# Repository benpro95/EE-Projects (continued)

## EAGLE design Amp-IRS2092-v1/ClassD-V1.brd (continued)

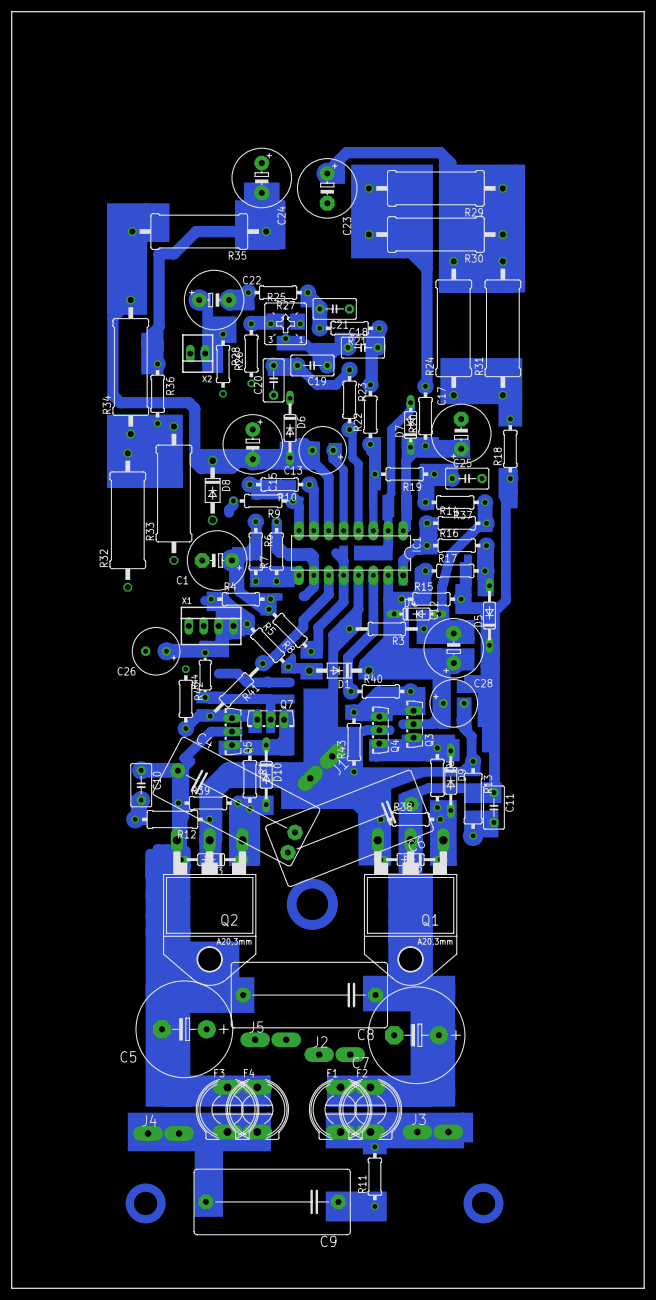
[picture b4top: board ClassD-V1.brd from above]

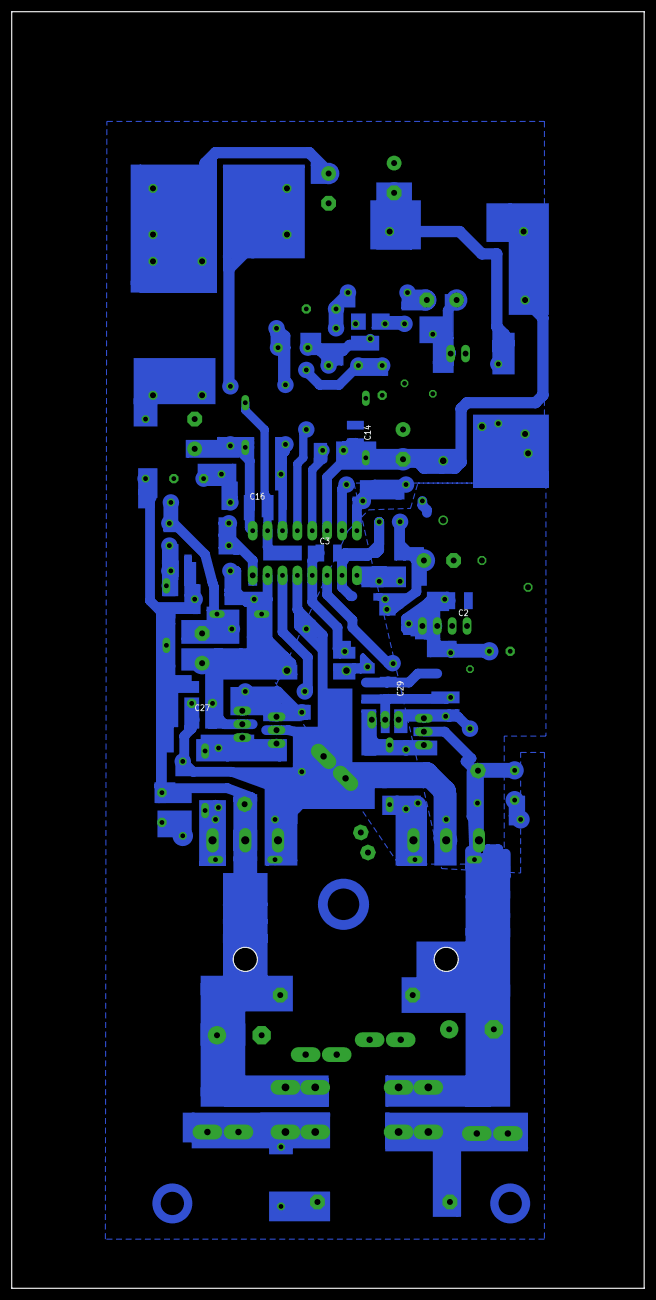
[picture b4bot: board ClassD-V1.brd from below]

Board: 2 copper layers, 107.9 x 217.9 mm, 101 parts (6 on the bottom side), 47 nets.

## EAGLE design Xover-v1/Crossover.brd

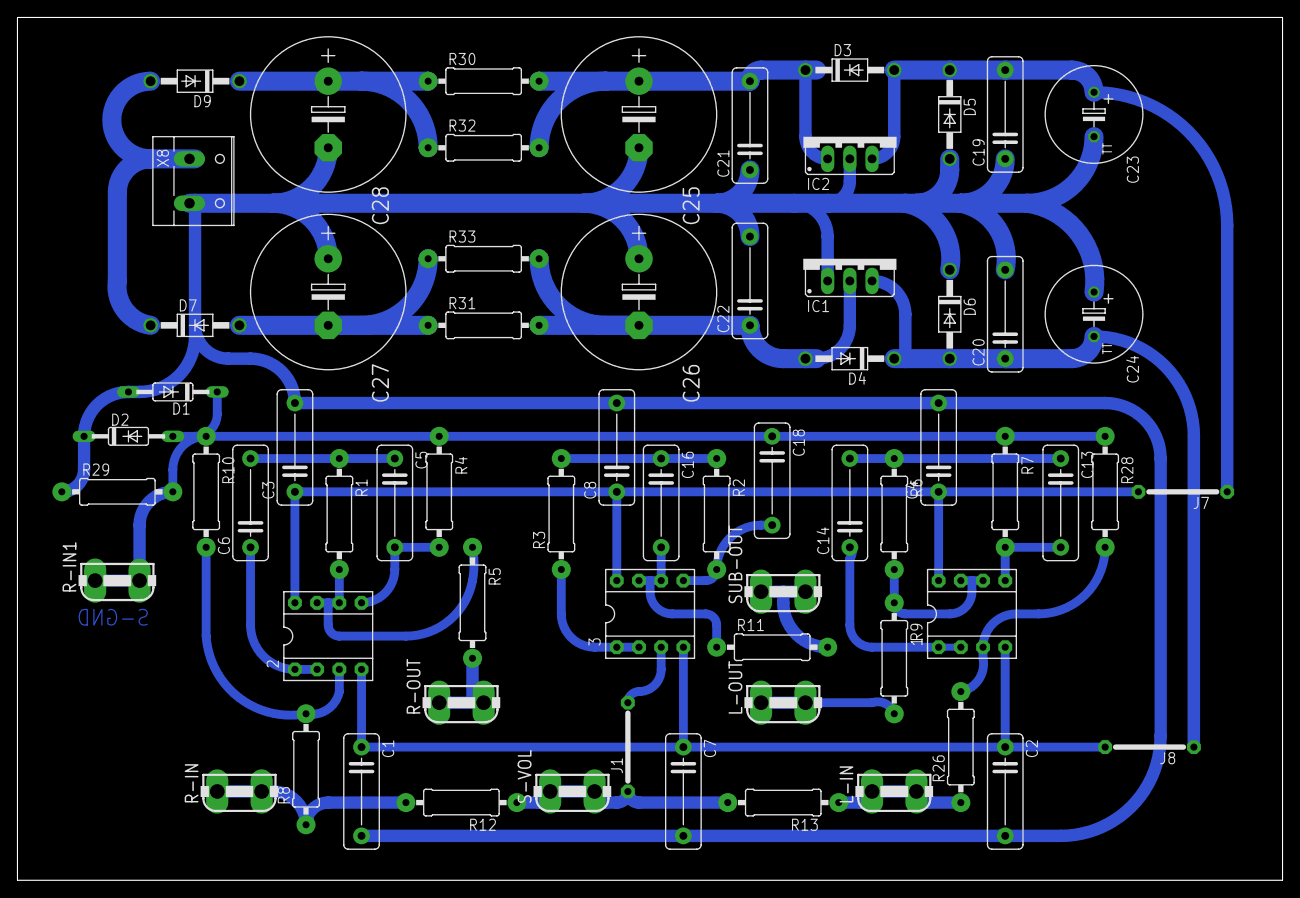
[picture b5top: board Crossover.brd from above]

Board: 2 copper layers, 144.8 x 98.7 mm, 66 parts (0 on the bottom side), 32 nets.

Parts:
1, 2, 3: OPA2132; DIP-8
C1, C2, C3, C4, C5, C6, C7, C8, C13, C14, C16, C18, C19, C20, C21, C22: .1; C102-043X133
C23, C24: 470uF; TT5D11
C25, C26, C27, C28: 4700uF; E7,5-18
D1, D2: 1N4148; DO35-10
D3, D4, D5, D6, D7, D9: 1N4004; DO41-10
IC1: 7915; 79XXS
IC2: 7815; 78XXS
J1, J7, J8: J10MM; 10
L-IN: QFIT; FASTON
L-OUT: QFIT; FASTON
R1, R2, R3, R4, R6, R7: 8.2k; 0309/12
R5, R9, R11: 100R; 0309/12
R8, R26: 2.2K; 0309/12
R10, R28: 100K; 0309/12
R12, R13: 10K; 0309/12
R29: 10R; 0309/12
R30, R31, R32, R33: 22R; 0309/12
R-IN, R-IN1: QFIT; FASTON
R-OUT: QFIT; FASTON
S-VOL: QFIT; FASTON
SUB-OUT: QFIT; FASTON
X8: 16VAC; W237-132

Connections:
+15V: 1.8, 2.8, 3.8, C3.1, C4.1, C8.1, J7.2
-15V: 1.4, 2.4, 3.4, C1.1, C2.1, C7.1, J8.2
AGND: C18.1, D1.C, D2.A, R4.1, R7.1, R10.1, R28.1, R29.2, R-IN1.1, R-IN1.2
GND: C1.2, C2.2, C3.2, C4.2, C7.2, C8.2, C19.1, C20.2, C21.1, C22.2, C23.-, C24.+, C25.-, C26.+, C27.+, C28.-, D1.A, D2.C, D5.A, D6.C, IC1.GND, IC2.GND, R29.1, X8.2
unnamed: 1.1, 1.2, C14.1
unnamed: 3.6, 3.7, C16.2, R11.1
unnamed: 1.6, 1.7, R6.2, R9.1
unnamed: 2.1, 2.2, C6.1
unnamed: 2.6, 2.7, R1.2, R5.1
unnamed: 2.5, C5.2, R4.2
unnamed: 3.5, C18.2, R2.2
unnamed: C5.1, C6.2, R1.1
unnamed: R5.2, R-OUT.1, R-OUT.2
unnamed: 2.3, R8.2, R10.2
unnamed: R8.1, R12.2, R-IN.1, R-IN.2
unnamed: 1.5, C13.2, R7.2
unnamed: 3.1, 3.2, R3.1
unnamed: C13.1, C14.2, R6.1
unnamed: C16.1, R2.1, R3.2
unnamed: R11.2, SUB-OUT.1, SUB-OUT.2
unnamed: L-OUT.1, L-OUT.2, R9.2
unnamed: 3.3, J1.2
unnamed: J1.1, R12.1, R13.2, S-VOL.1, S-VOL.2
unnamed: 1.3, R26.2, R28.2
unnamed: L-IN.1, L-IN.2, R13.1, R26.1
unnamed: C27.-, D7.A, R31.1, R33.1
unnamed: C21.2, C25.+, D3.C, IC2.IN, R30.2, R32.2
unnamed: C19.2, C23.+, D3.A, D5.C, IC2.OUT, J7.1
unnamed: C22.1, C26.-, D4.A, IC1.IN, R31.2, R33.2
unnamed: D7.C, D9.A, X8.1
unnamed: C28.+, D9.C, R30.1, R32.1
unnamed: C20.1, C24.-, D4.C, D6.A, IC1.OUT, J8.1

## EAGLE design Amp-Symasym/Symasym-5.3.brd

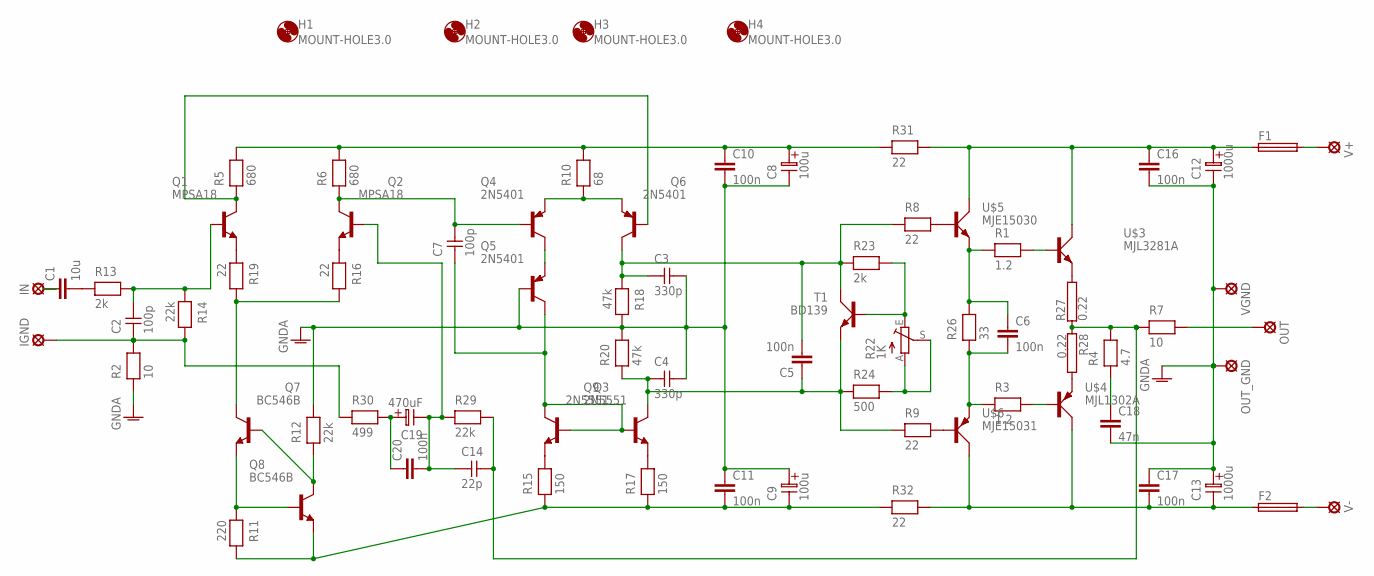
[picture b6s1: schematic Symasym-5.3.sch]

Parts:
C1: 10u; C5B7.2
C2, C7: 100p; C-3,75
C3, C4: 330p; C-3,75
C5: 100n; C5B2.5
C6, C16, C17, C20: 100n; C5B3
C8, C9: 100u; ES-5
C10, C11: 100n; C5B3.5
C12, C13: 1000u; ES-7,5
C14: 22p; C-3,75
C18: 47n; C5B3
C19: 470uF; ES-5
F1, F2: SHK20L
H1, H2, H3, H4: MOUNT-HOLE3.0; 3,0
IGND: SE11
IN: SE11
OUT: SE11
OUT_GND: SE11
Q1, Q2: MPSA18; TO92-EBC@1
Q3, Q9: 2N5551; TO92-EBC@1
Q4, Q5, Q6: 2N5401; TO92-EBC
Q7, Q8: BC546B; TO92-EBC
R1, R3: 1.2; R-18
R2: 10; R-10
R4: 4.7; R-18
R5, R6: 680; R-10
R7: 10; R-18
R8, R9, R31, R32: 22; R-10
R10: 68; R-10
R11: 220; RS-2,5
R12, R29: 22k; R-10
R13: 2k; RS-2,5
R14: 22k; RS-2,5
R15, R17: 150; R-10
R16, R19: 22; RS-2,5
R18, R20: 47k; RS-2,5
R22: 1K; LI10
R23: 2k; R-10
R24: 500; R-10
R26: 33; R-10
R27, R28: 0.22; KH208R-8
R30: 499; R-10
T1: BD139; TO126AV
U$3: MJL3281A; TO247BV
U$4: MJL1302A; TO247BV
U$5: MJE15030; TO220AV
U$6: MJE15031; TO220AV
V+: SE11
V-: SE11
VGND: SE11

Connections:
+24V: C8.1, C10.1, R5.2, R6.2, R10.2, R31.1
-24V: C9.2, C11.2, Q8.E, R11.2, R15.1, R17.1, R32.1
unnamed: Q3.E, R15.2
unnamed: R1.2, U$3.G (B)
unnamed: Q7.C, R16.2, R19.2
unnamed: Q4.C, Q5.E
unnamed: R3.2, U$4.G (B)
unnamed: Q9.E, R17.2
unnamed: C12.1, C16.1, F1.1A, R31.2, U$3.D (C), U$5.C
unnamed: C7.P$2 (2), Q2.C, Q4.B, R6.1
unnamed: C3.P$1 (1), C5.2, Q6.C, R8.1, R18.1, R23.1, T1.C
unnamed: C7.P$1 (1), Q3.B, Q3.C, Q5.C, Q9.B
unnamed: R8.2, U$5.B
unnamed: R9.2, U$6.B
unnamed: C1.2, R13.1
unnamed: C18.1, R4.1
unnamed: C2.P$1 (1), IGND.MP, R2.2, R14.2, R30.1
unnamed: Q7.E, Q8.B, R11.1
unnamed: Q4.E, Q6.E, R10.1
unnamed: Q7.B, Q8.C, R12.1
unnamed: C1.1, IN.MP
unnamed: C2.P$2 (2), Q1.B, R13.2, R14.1
unnamed: Q1.C, Q6.B, R5.1
unnamed: C19.1, C20.1, R30.2
unnamed: R22.E, R23.2, T1.B
unnamed: R22.A, R22.S, R24.2
unnamed: C13.2, C17.2, F2.1A, R32.2, U$4.D (C), U$6.C
unnamed: C14.P$1 (1), C19.2, C20.2, Q2.B, R29.1
unnamed: OUT.MP, R7.2
unnamed: R27.2, U$3.S (E)
unnamed: R28.2, U$4.S (E)
unnamed: C14.P$2 (2), R4.2, R7.1, R27.1, R28.1, R29.2
unnamed: F2.2A, V-.MP
unnamed: C4.P$1 (1), C5.1, Q9.C, R9.1, R20.1, R24.1, T1.E
unnamed: F1.2A, V+.MP
unnamed: C6.1, R1.1, R26.2, U$5.E
unnamed: C6.2, R3.1, R26.1, U$6.E
unnamed: C3.P$2 (2), C4.P$2 (2), C8.2, C9.1, C10.2, C11.1, C12.2, C13.1, C16.2, C17.1, C18.2, OUT_GND.MP, Q5.B, R2.1, R12.2, R18.2, R20.2, VGND.MP
unnamed: Q2.E, R16.1
unnamed: Q1.E, R19.1

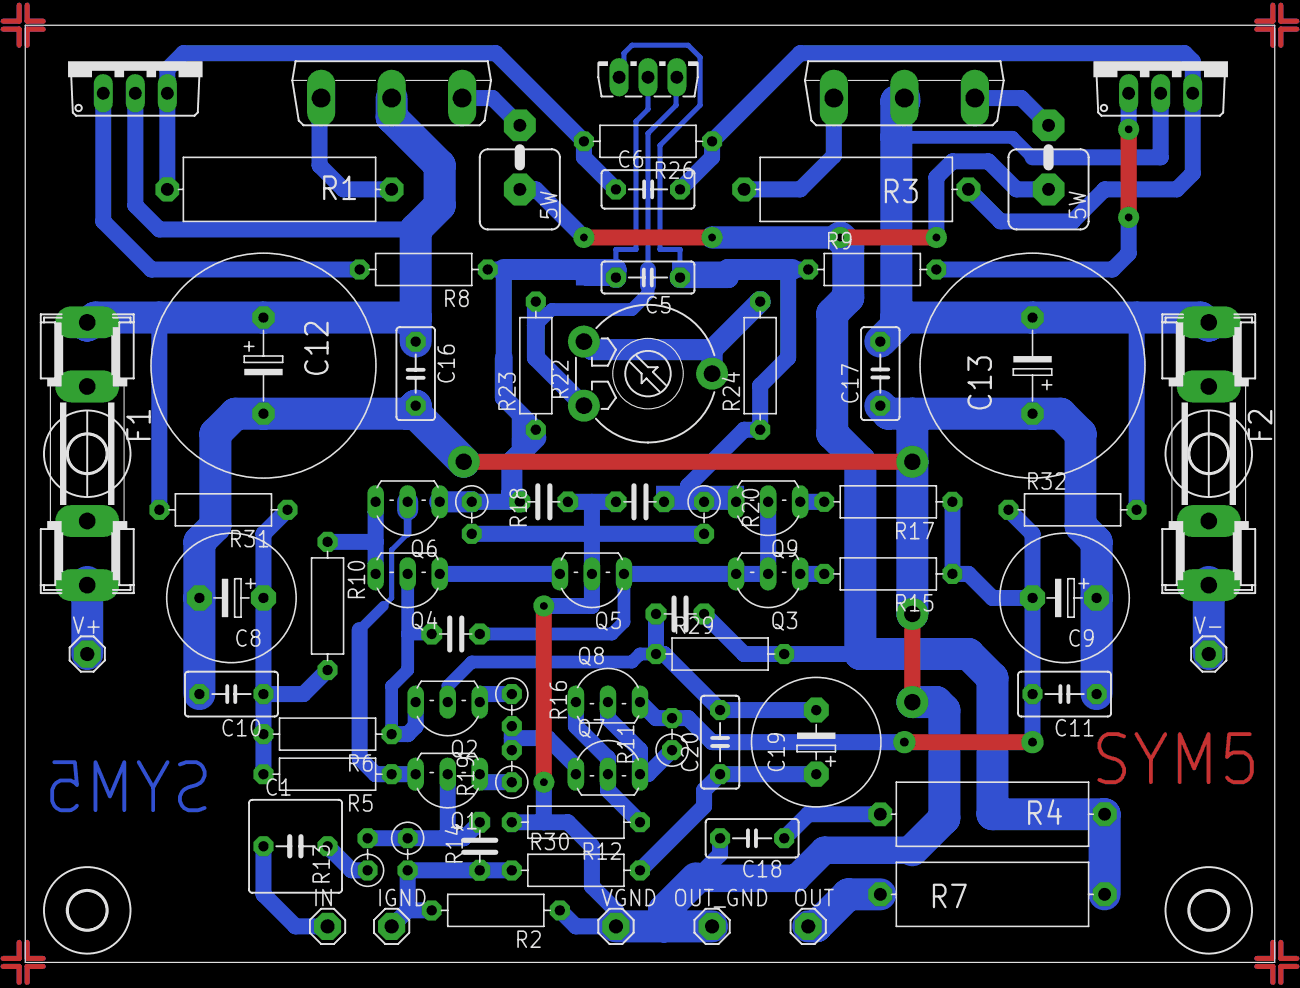
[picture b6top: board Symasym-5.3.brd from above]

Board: 2 copper layers, 99.0 x 74.3 mm, 76 parts (0 on the bottom side), 40 nets.

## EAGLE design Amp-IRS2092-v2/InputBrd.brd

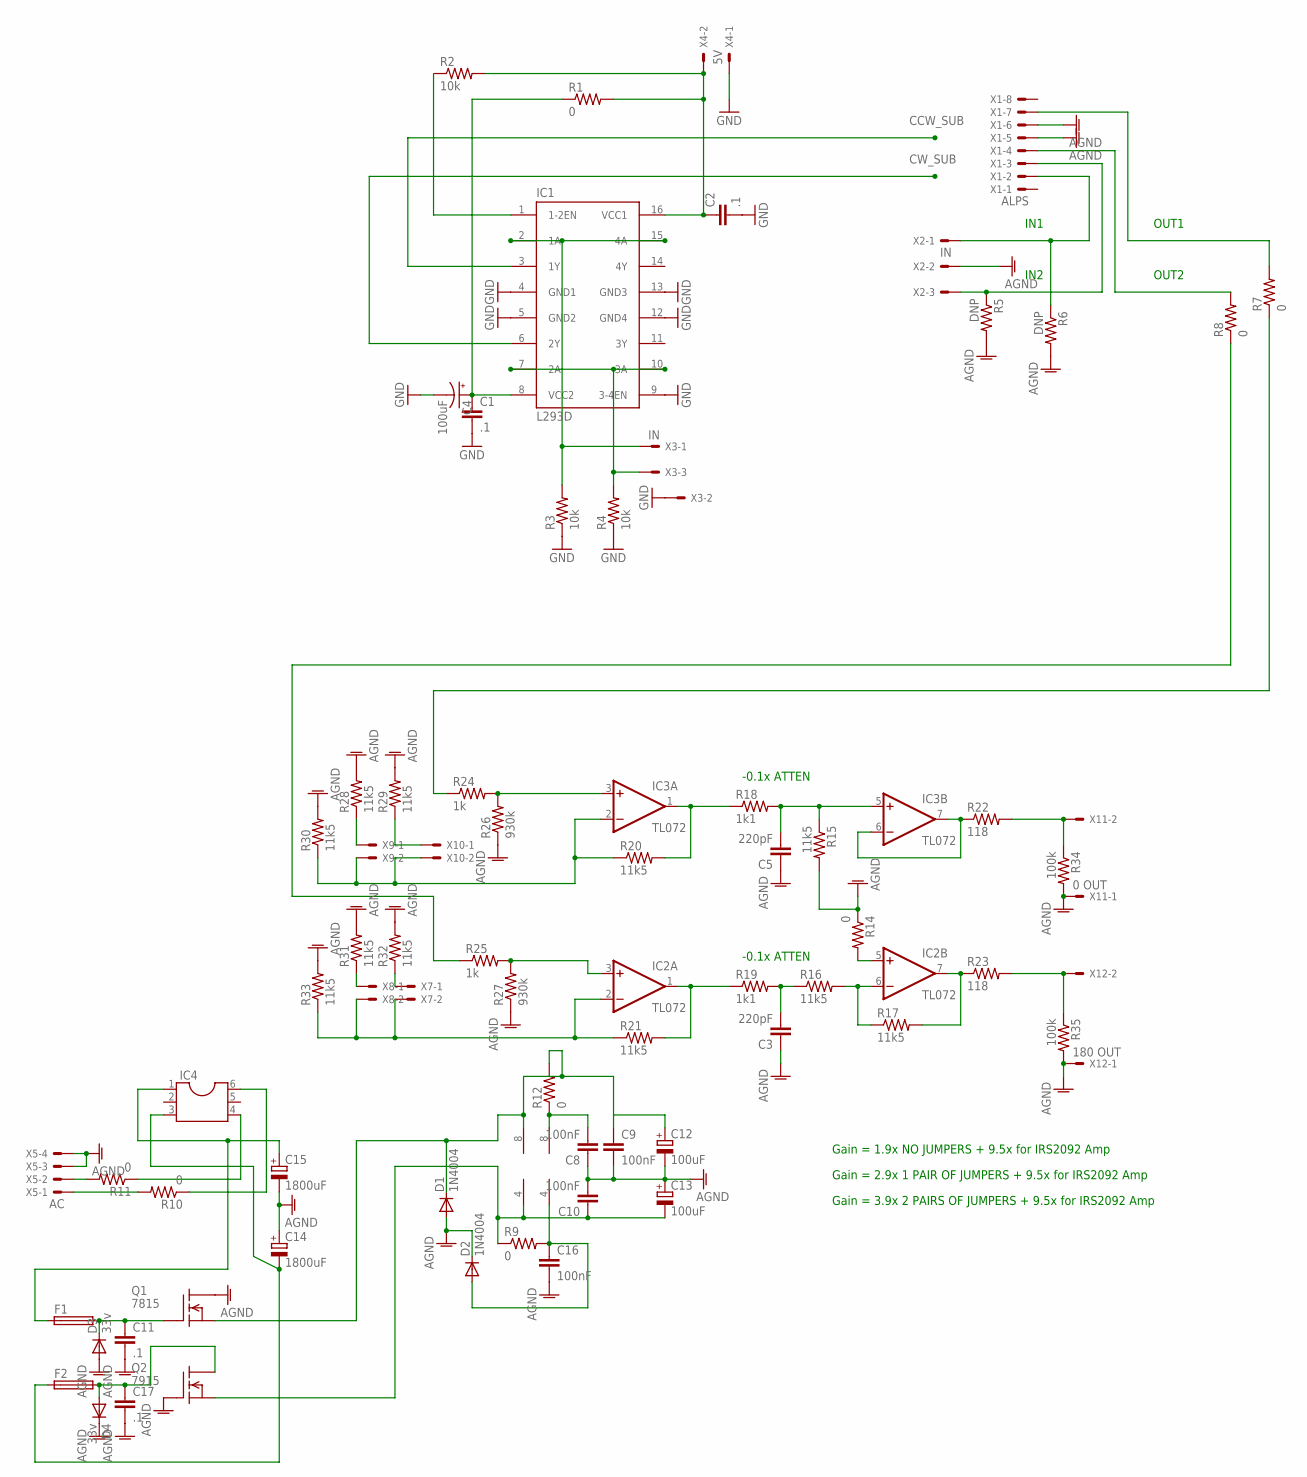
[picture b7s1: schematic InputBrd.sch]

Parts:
C1, C2, C11, C17: .1; C1210
C3, C5: 220pF; C050-035X075
C4: 100uF; E2,5-6E
C8, C9, C10, C16: 100nF; C1210
C12, C13: 100uF; E3,5-10
C14, C15: 1800uF; E7,5-16
D1, D2: 1N4004; DO41-10
D3, D4: 33v; TO220ACS
F1, F2: 19560
IC1: L293D; DIL16
IC2, IC3: TL072; DIL08
IC4: DIL6; DIL06
Q1: 7815; TO220
Q2: 7915; TO220
R1: 0; 0207/15
R2, R3, R4: 10k; R1210
R5, R6: DNP; 0309/10
R7, R8, R14: 0; 0309/12
R9, R12: 0; 0309/10
R10, R11: 0; 0309V
R15: 11k5; 0309/12
R16, R17, R20, R21, R28, R29, R30, R31, R32, R33: 11k5; 0309/10
R18, R19: 1k1; 0309/12
R22: 118; 0309/12
R23: 118; 0309/10
R24: 1k; 0411/15
R25: 1k; 0309/12
R26, R27: 930k; 0309/10
R34: 100k; 0309/12
R35: 100k; 0309/10
X1: ALPS; 22-23-2081
X2, X3: IN; 22-23-2031
X4: 5V; 22-23-2021
X5: AC; 5566-4
X7, X8, X9, X10: 22-23-2021
X11: 0 OUT; 22-23-2021
X12: 180 OUT; 22-23-2021

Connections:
AGND: C3.1, C5.1, C8.1, C9.2, C10.2, C11.2, C12.-, C13.+, C14.+, C15.-, C16.2, C17.2, D1.A, D2.C, D3.A, D4.C, Q1.2 (D), Q2.1 (G), R5.2, R6.2, R14.1, R15.2, R26.1, R27.1, R28.2, R29.2, R30.2, R31.2, R32.2, R33.2, R34.2, R35.2, X1.5, X1.6, X2.2, X5.3, X5.4, X11.1, X12.1
CCW_SUB: IC1.3 (1Y)
CW_SUB: IC1.6 (2Y)
GND: C1.2, C2.2, C4.-, IC1.4 (GND1), IC1.5 (GND2), IC1.9 (3-4EN), IC1.12 (GND4), IC1.13 (GND3), R3.1, R4.1, X3.2, X4.1
unnamed: IC1.7 (2A), IC1.10 (3A), R4.2, X3.3
unnamed: IC1.2 (1A), IC1.15 (4A), R3.2, X3.1
unnamed: R6.1, X1.2, X2.1
unnamed: R7.2, X1.7
unnamed: R5.1, X1.3, X2.3
unnamed: R7.1, R24.1
unnamed: IC1.1 (1-2EN), R2.1
unnamed: C1.1, C4.+, IC1.8 (VCC2), R1.1
unnamed: R8.2, X1.4
unnamed: C11.1, D3.C, F1.2, Q1.1 (G)
unnamed: C2.1, IC1.16 (VCC1), R1.2, R2.2, X4.2
unnamed: C17.1, D4.A, F2.2, Q2.2 (D)
unnamed: C16.1, D2.A, IC3.4 (V-), R9.2
unnamed: C8.2, IC3.8 (V+), R12.1
unnamed: R11.2, X5.2
unnamed: R10.2, X5.1
unnamed: IC4.6, R10.1
unnamed: IC4.4, R11.1
unnamed: C15.+, F1.1, IC4.1
unnamed: C14.-, F2.1, IC4.3
unnamed: C9.1, C12.+, D1.C, IC2.8 (V+), Q1.3 (S), R12.2
unnamed: C10.1, C13.-, IC2.4 (V-), Q2.3 (S), R9.1
unnamed: IC3.6 (-IN), IC3.7 (OUT), R22.1
unnamed: IC2.5 (+IN), R14.2
unnamed: C5.2, IC3.5 (+IN), R15.1, R18.2
unnamed: IC2.6 (-IN), R16.2, R17.1
unnamed: IC2.7 (OUT), R17.2, R23.1
unnamed: C3.2, R16.1, R19.2
unnamed: IC3.1 (OUT), R18.1, R20.2
unnamed: IC2.1 (OUT), R19.1, R21.2
unnamed: IC3.3 (+IN), R24.2, R26.2
unnamed: IC3.2 (-IN), R20.1, R30.1, X9.2, X10.2
unnamed: IC2.2 (-IN), R21.1, R33.1, X7.2, X8.2
unnamed: IC2.3 (+IN), R25.2, R27.2
unnamed: R31.1, X8.1
unnamed: R32.1, X7.1
unnamed: R29.1, X10.1
unnamed: R28.1, X9.1
unnamed: R22.2, R34.1, X11.2
unnamed: R23.2, R35.1, X12.2
unnamed: R8.1, R25.1

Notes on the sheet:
IN1
IN2
OUT2
OUT1
Gain = 1.9x NO JUMPERS + 9.5x for IRS2092 Amp
Gain = 2.9x 1 PAIR OF JUMPERS + 9.5x for IRS2092 Amp
Gain = 3.9x 2 PAIRS OF JUMPERS + 9.5x for IRS2092 Amp
-0.1x ATTEN

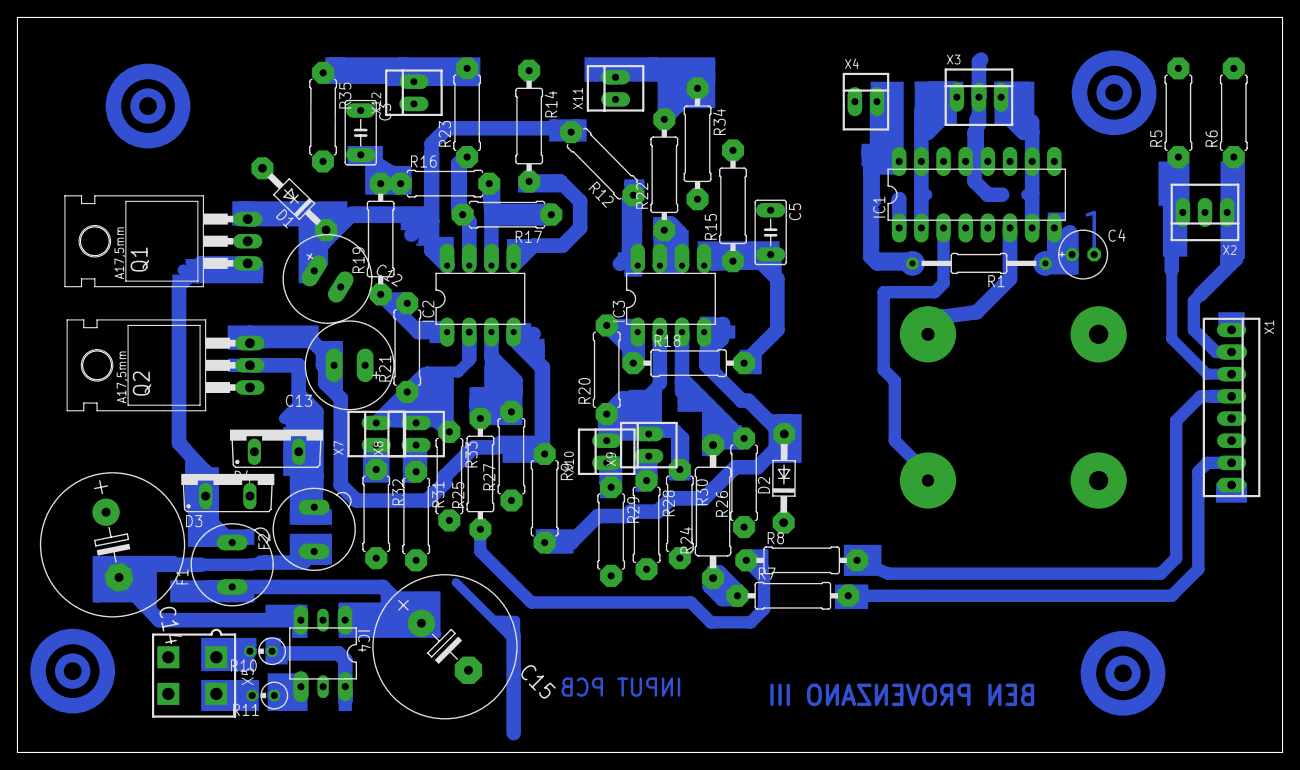
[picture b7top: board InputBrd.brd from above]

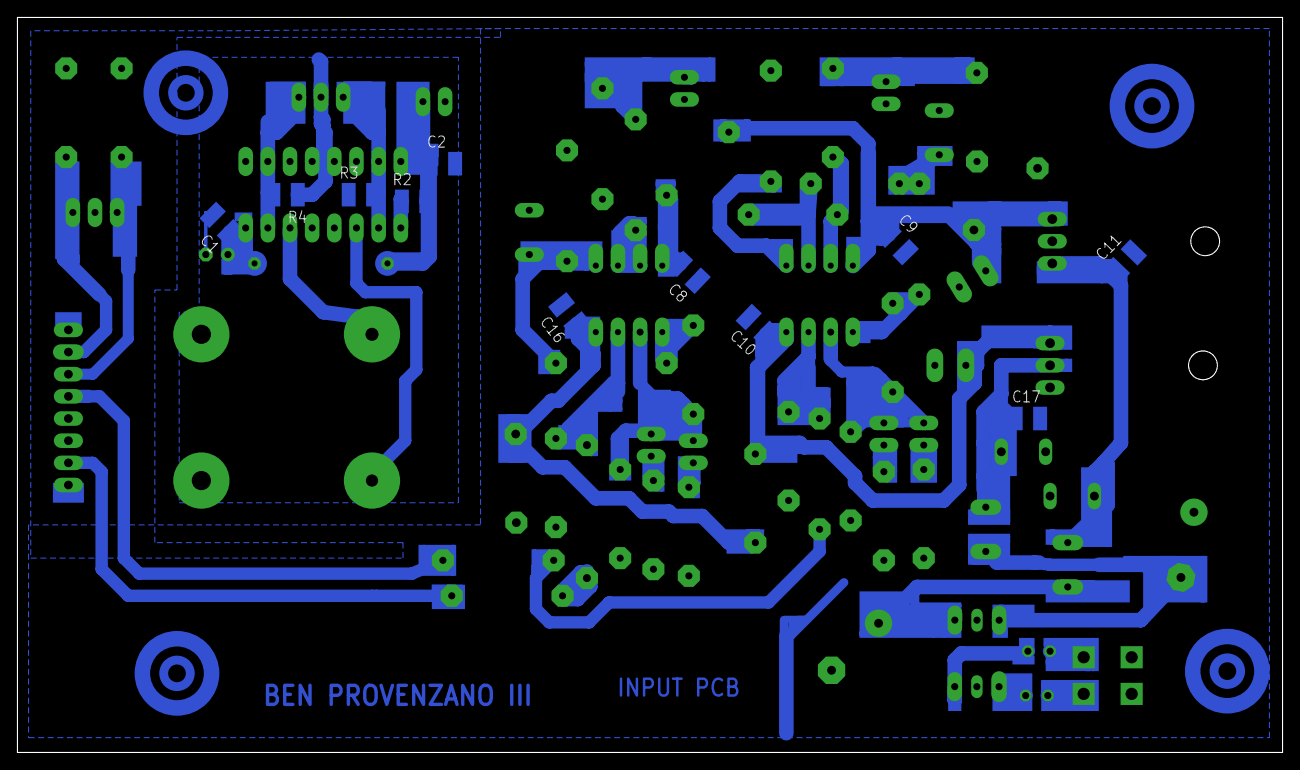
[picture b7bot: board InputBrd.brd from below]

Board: 2 copper layers, 145.0 x 84.3 mm, 72 parts (11 on the bottom side), 43 nets.

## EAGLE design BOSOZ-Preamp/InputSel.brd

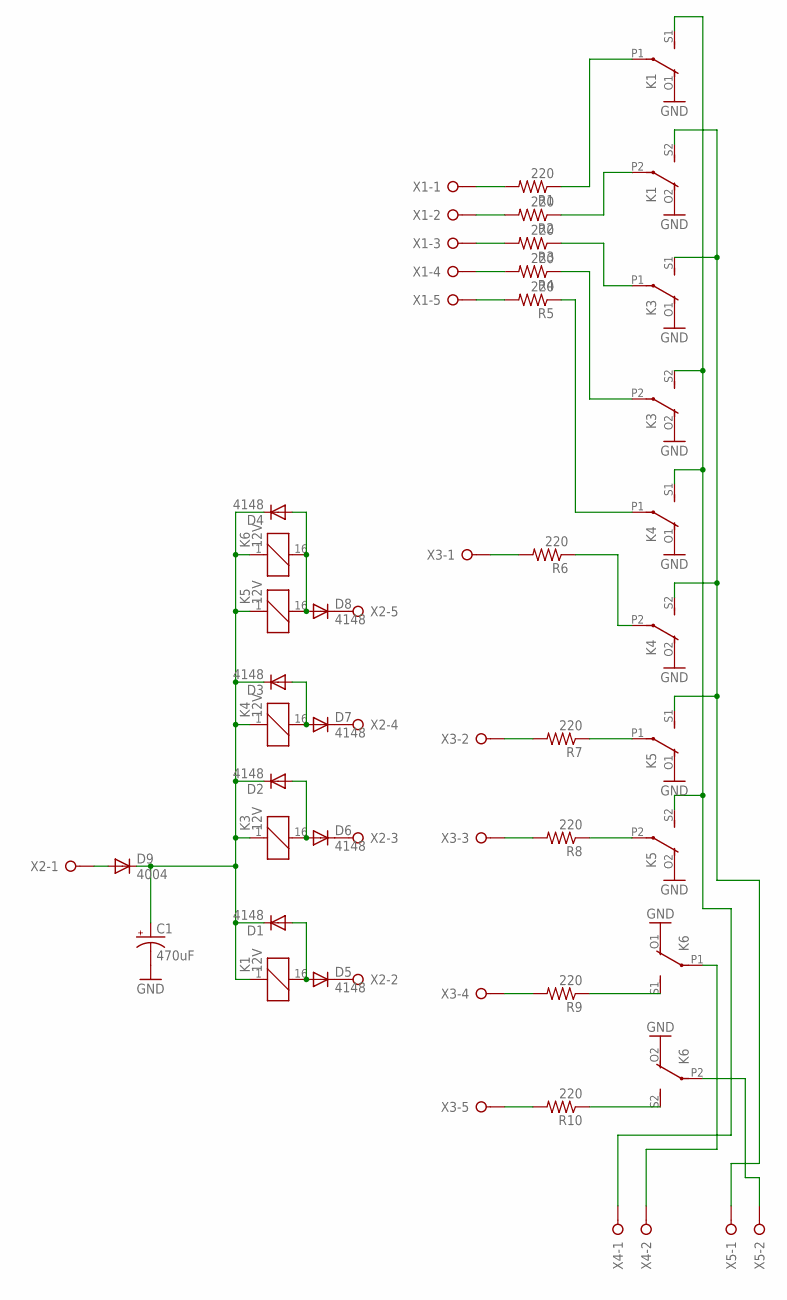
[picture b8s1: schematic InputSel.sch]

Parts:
C1: 470uF; E5-10,5
D1, D2, D3, D4, D5, D6, D7, D8: 4148; DO35-7
D9: 4004; DO35-10
K1, K3, K4, K5, K6: 12V; G6A-234P
R1, R2, R3, R4, R5, R6, R7, R8, R9, R10: 220; 0207/10
X1, X2, X3: W237-05P; W237-5P
X4, X5: W237-02P; W237-132

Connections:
GND: C1.-, K1.O1 (O), K1.O2 (O), K3.O1 (O), K3.O2 (O), K4.O1 (O), K4.O2 (O), K5.O1 (O), K5.O2 (O), K6.O1 (O), K6.O2 (O)
unnamed: K3.P1, R3.1
unnamed: R1.2, X1.1
unnamed: K3.P2, R4.1
unnamed: R2.2, X1.2
unnamed: K1.S1 (S), K3.S2 (S), K4.S1 (S), K5.S2 (S), X4.1
unnamed: R3.2, X1.3
unnamed: R4.2, X1.4
unnamed: K1.S2 (S), K3.S1 (S), K4.S2 (S), K5.S1 (S), X5.1
unnamed: K1.P2, R2.1
unnamed: K1.P1, R1.1
unnamed: R5.2, X1.5
unnamed: K4.P1, R5.1
unnamed: K5.P2, R8.1
unnamed: K5.P1, R7.1
unnamed: K4.P2, R6.1
unnamed: R6.2, X3.1
unnamed: R7.2, X3.2
unnamed: R8.2, X3.3
unnamed: R9.2, X3.4
unnamed: K6.S1 (S), R9.1
unnamed: R10.2, X3.5
unnamed: K6.S2 (S), R10.1
unnamed: C1.+, D1.C, D2.C, D3.C, D4.C, D9.C, K1.1, K3.1, K4.1, K5.1, K6.1
unnamed: K6.P1, X4.2
unnamed: K6.P2, X5.2
unnamed: D4.A, D8.A, K5.16 (2), K6.16 (2)
unnamed: D1.A, D5.A, K1.16 (2)
unnamed: D2.A, D6.A, K3.16 (2)
unnamed: D3.A, D7.A, K4.16 (2)
unnamed: D5.C, X2.2
unnamed: D6.C, X2.3
unnamed: D8.C, X2.5
unnamed: D7.C, X2.4
unnamed: D9.A, X2.1

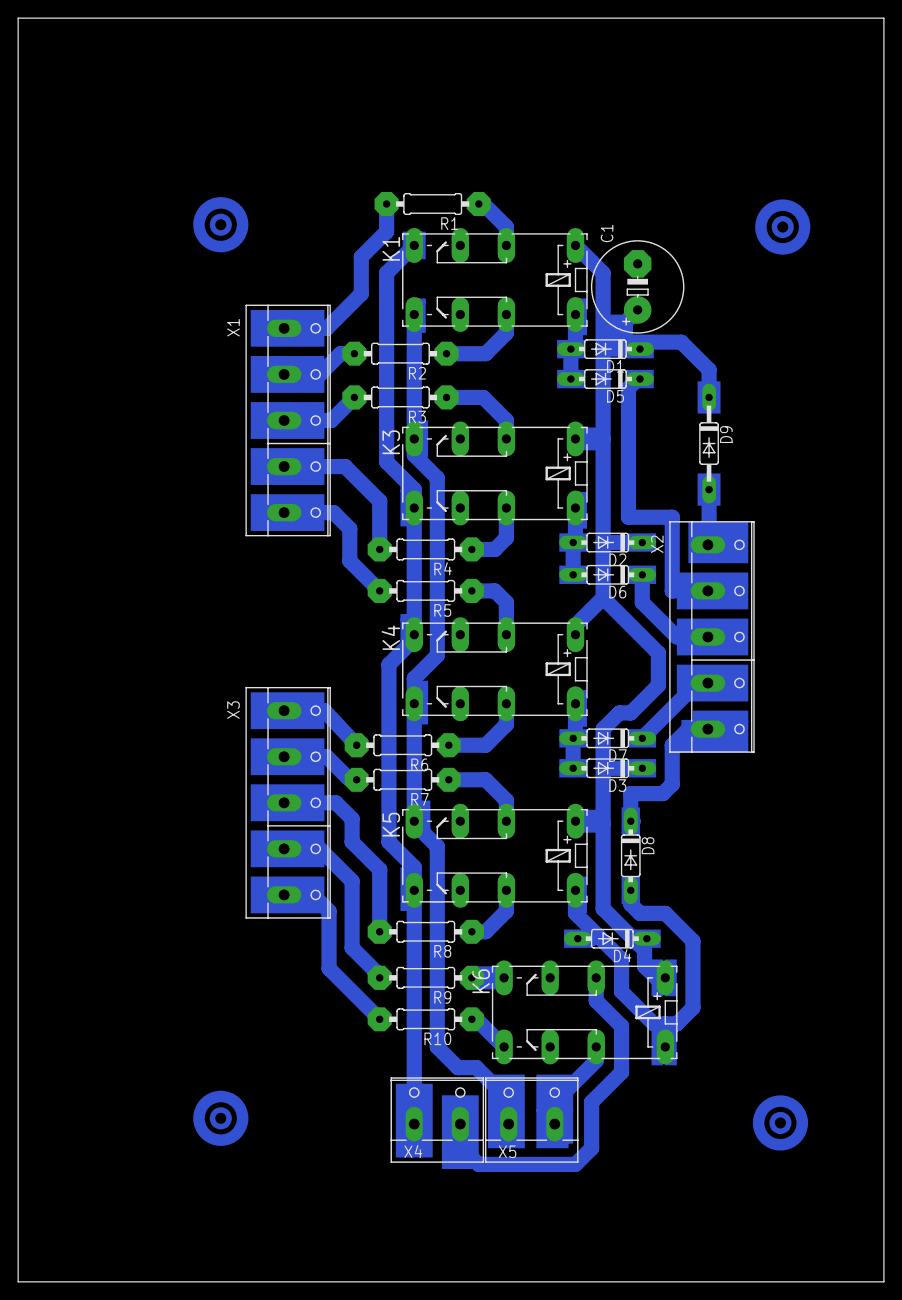
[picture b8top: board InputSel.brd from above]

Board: 2 copper layers, 95.5 x 139.4 mm, 30 parts (0 on the bottom side), 35 nets.

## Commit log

2022-11-02 2022-11-01 20:56
2022-11-02 2022-11-01 21:02
2022-11-11 2022-11-11 09:03
2022-11-12 2022-11-11 21:16
2022-11-12 2022-11-12 04:21
2022-11-12 2022-11-12 15:55
2022-11-15 2022-11-15 06:53
2022-11-15 2022-11-15 07:15
2022-11-15 2022-11-15 07:43
2022-11-15 2022-11-15 15:15
2022-11-19 2022-11-19 05:00
2022-11-25 2022-11-25 17:01
2022-11-26 2022-11-26 00:18
2022-11-26 2022-11-26 00:36
2022-12-02 2022-12-01 20:45
2022-12-10 2022-12-10 09:39
2022-12-10 2022-12-10 13:26
2022-12-11 2022-12-11 12:42
2022-12-12 2022-12-12 06:13
2022-12-12 2022-12-12 13:30
2022-12-13 2022-12-13 07:53
2022-12-13 2022-12-13 17:40
2022-12-14 2022-12-13 22:49
2022-12-14 2022-12-14 13:45
2022-12-14 2022-12-14 15:57
2022-12-14 2022-12-14 16:08
2022-12-15 2022-12-15 14:08
2022-12-16 2022-12-15 19:37
2022-12-16 2022-12-15 23:06
2022-12-16 2022-12-16 06:18
2022-12-16 2022-12-16 10:49
2022-12-18 2022-12-17 22:41
2022-12-18 2022-12-18 00:52
2022-12-19 2022-12-18 21:59
2022-12-19 2022-12-19 15:05
2022-12-20 2022-12-19 22:24
2022-12-20 2022-12-19 22:54
2022-12-20 2022-12-19 23:31
2022-12-20 2022-12-20 10:03
2022-12-20 2022-12-20 11:06
2022-12-21 2022-12-21 06:55
2022-12-21 2022-12-21 12:03
2022-12-21 2022-12-21 17:01
2022-12-21 2022-12-21 17:14
2022-12-22 2022-12-21 20:03
2022-12-22 2022-12-21 21:08
2022-12-22 2022-12-21 21:27
2022-12-22 2022-12-21 21:28
2022-12-23 2022-12-23 09:33
2022-12-23 2022-12-23 14:15
2022-12-26 2022-12-25 19:55
2022-12-26 2022-12-26 11:24
2022-12-27 2022-12-27 11:16
2022-12-30 2022-12-30 08:26
2022-12-31 2022-12-31 07:51
2022-12-31 2022-12-31 08:42
2022-12-31 2022-12-31 10:10
2022-12-31 2022-12-31 11:21
2023-01-01 2022-12-31 20:19
2023-01-01 2023-01-01 06:55
2023-01-04 2023-01-04 05:10
2023-01-04 2023-01-04 07:08
2023-01-06 2023-01-06 01:57
2023-01-07 2023-01-07 05:01
2023-01-07 2023-01-07 17:03
2023-01-08 2023-01-07 19:43
2023-01-13 2023-01-13 06:34
2023-01-13 2023-01-13 06:47
2023-01-25 2023-01-25 05:36
2023-02-04 2023-02-03 23:56
2023-02-06 2023-02-06 11:32
2023-02-12 2023-02-12 08:04
2023-02-13 2023-02-13 14:56
2023-02-20 2023-02-20 11:50
2023-02-26 2023-02-26 17:27
2023-04-04 2023-04-03 20:28
2023-04-04 2023-04-03 20:30
2023-04-04 2023-04-03 21:24
2023-04-05 2023-04-04 21:51
2023-04-07 2023-04-07 15:28
2023-04-14 2023-04-13 21:15
2023-04-23 2023-04-22 21:32
2023-04-24 2023-04-24 11:49
2023-04-24 2023-04-24 12:02
2023-04-24 2023-04-24 12:31
2023-04-24 2023-04-24 14:15
2023-04-26 2023-04-25 20:33
2023-05-18 2023-05-17 21:27
2023-05-18 2023-05-18 08:48
2023-05-18 2023-05-18 08:49
2023-05-18 2023-05-18 19:05
2023-05-27 2023-05-27 09:22
2023-05-27 2023-05-27 09:26
2023-06-02 2023-06-02 04:45
2023-06-11 2023-06-10 22:36
2023-06-11 2023-06-10 22:46
2023-06-13 2023-06-12 20:24
2023-06-18 2023-06-17 22:12
2023-06-19 2023-06-18 22:30
2023-06-24 2023-06-23 20:52
2023-06-24 2023-06-24 10:19
2023-06-24 2023-06-24 10:24
2023-06-24 2023-06-24 16:25
2023-06-30 2023-06-30 07:35
2023-06-30 2023-06-30 17:09
2023-07-01 2023-06-30 23:40
2023-07-01 2023-07-01 00:55
2023-07-01 2023-07-01 09:48
2023-07-01 2023-07-01 11:25
2023-07-01 2023-07-01 19:52
2023-07-01 2023-07-01 19:58
2023-07-02 2023-07-02 07:32
2023-07-02 2023-07-02 19:44
2023-07-03 2023-07-02 20:09
2023-07-03 2023-07-02 20:20
2023-07-03 2023-07-02 21:17
2023-07-03 2023-07-02 21:25
2023-07-04 2023-07-04 08:37
2023-07-10 2023-07-09 23:06
2023-07-10 2023-07-10 07:45
2023-08-07 2023-08-06 21:44
2023-08-11 2023-08-10 21:30
2023-08-26 2023-08-26 06:57
2023-09-01 2023-09-01 06:12
2023-09-06 2023-09-05 20:45
2023-09-07 2023-09-06 21:05
2023-09-07 2023-09-06 22:15
2023-09-19 2023-09-19 18:16
2023-09-21 2023-09-21 19:33
2023-09-22 2023-09-22 14:25
2023-09-30 2023-09-30 15:44
2023-10-01 2023-10-01 11:25
2023-10-14 2023-10-14 10:54
2023-10-19 2023-10-18 20:15
2023-10-21 2023-10-21 06:40
2023-10-23 2023-10-23 18:07
2024-01-11 2024-01-10 21:24
2024-01-14 2024-01-13 20:14
2024-04-07 2024-04-06 21:56
2024-04-07 2024-04-07 00:16
2024-04-07 2024-04-07 11:08
2024-04-07 2024-04-07 11:44
2024-04-07 2024-04-07 12:03
2024-04-09 2024-04-08 21:35
2024-04-09 2024-04-08 21:54
2024-04-09 2024-04-08 22:01
2024-04-09 2024-04-09 19:52
2024-05-27 2024-05-27 19:51
2024-06-14 2024-06-13 21:57
2024-06-15 2024-06-15 10:49
2024-06-21 2024-06-21 19:56
2024-06-22 2024-06-21 21:47
2024-06-22 2024-06-21 22:34
2024-06-22 2024-06-21 22:52
2024-06-22 2024-06-21 22:55
2024-06-22 2024-06-22 09:12
2024-06-22 2024-06-22 09:40
2024-06-22 2024-06-22 10:55
2024-07-13 2024-07-13 19:47
2024-08-26 2024-08-26 07:41
2024-08-31 2024-08-30 23:14
2024-09-08 2024-09-08 11:19
2024-09-10 2024-09-10 14:36
2024-09-15 2024-09-15 11:05
2024-09-18 2024-09-17 20:09
2024-09-20 2024-09-20 16:12
2024-09-24 2024-09-23 22:43
2024-09-29 2024-09-29 14:28
2024-10-02 2024-10-02 16:38
2024-10-12 2024-10-11 23:13
2024-10-12 2024-10-12 11:04
2024-10-12 2024-10-12 19:05
2024-10-13 2024-10-12 20:30
2024-10-19 2024-10-19 09:18
2024-11-04 2024-11-04 07:28
2024-11-04 2024-11-04 11:21
2024-11-06 2024-11-05 20:22
2024-11-12 2024-11-12 13:19
2024-11-12 2024-11-12 18:07
2024-11-14 2024-11-14 18:48
2024-11-15 2024-11-15 16:50
2024-11-21 2024-11-20 21:36
2024-11-24 2024-11-23 21:17
2024-11-25 2024-11-24 20:44
2024-11-25 2024-11-25 08:14
2024-11-26 2024-11-25 21:29
2024-11-28 2024-11-28 10:20
2024-11-30 2024-11-30 18:47
2024-12-02 2024-12-02 14:49
2024-12-04 2024-12-03 21:38
2024-12-07 2024-12-07 17:53
2024-12-09 2024-12-08 22:26
